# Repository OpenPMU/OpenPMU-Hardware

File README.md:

# OpenPMU Hardware
Reference materials for the OpenPMU V2 hardware for use by qualified professionals.

**Disclaimer:**  These files are **not** intended as a guide for how to build the hardware.  Such activities should only be conducted by suitably qualified professionals in a laboratory environment.

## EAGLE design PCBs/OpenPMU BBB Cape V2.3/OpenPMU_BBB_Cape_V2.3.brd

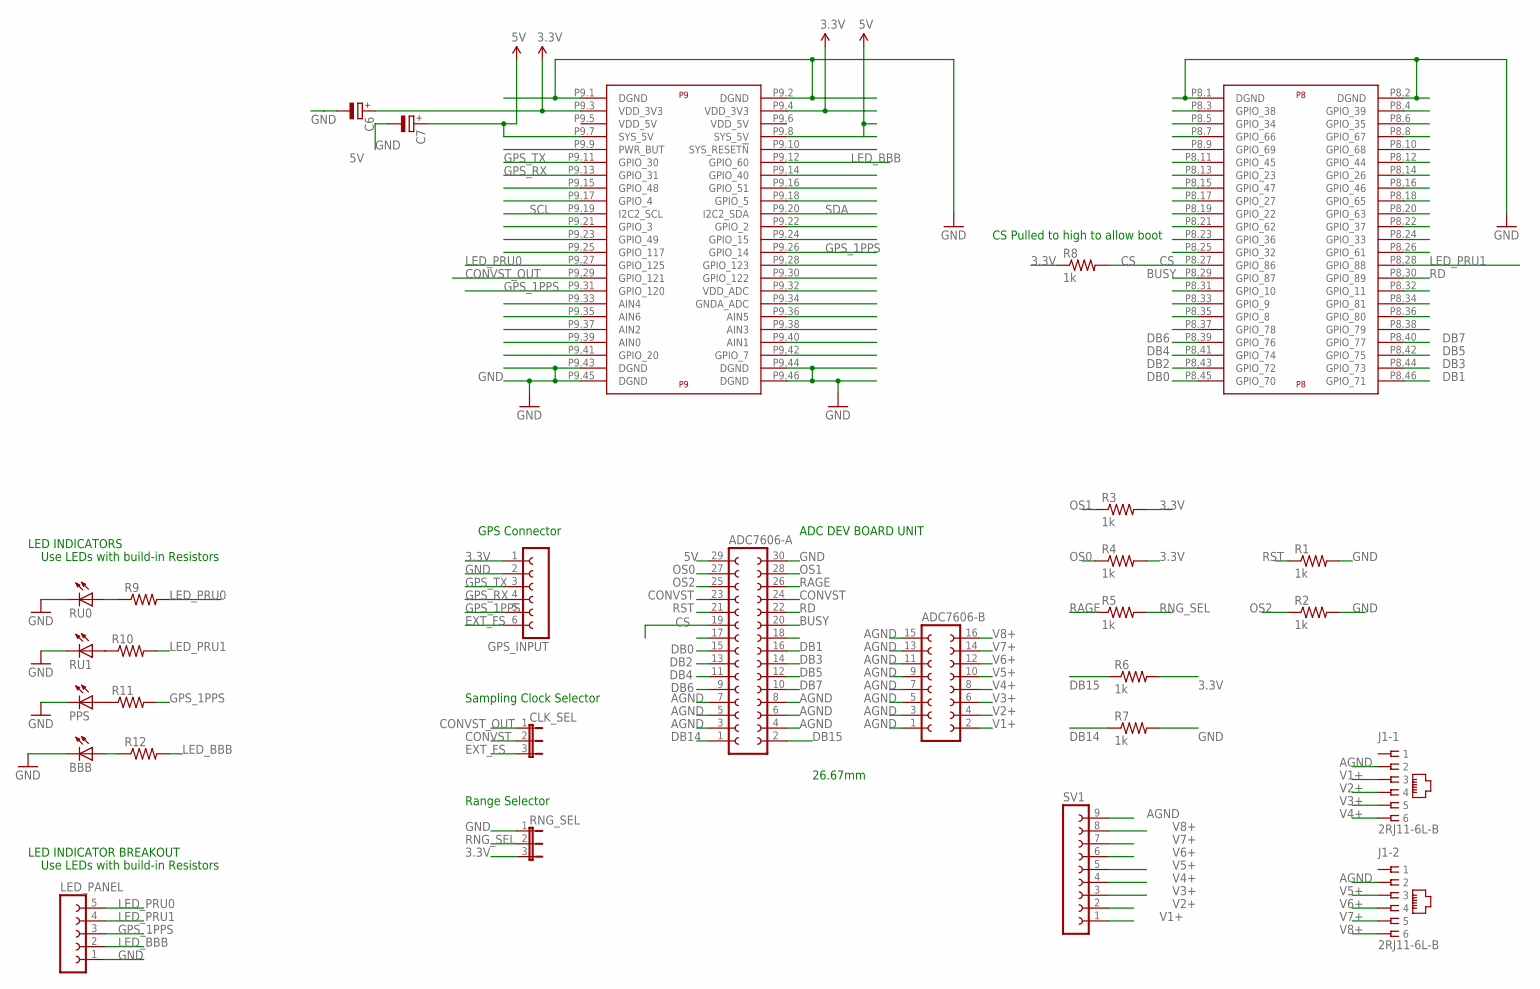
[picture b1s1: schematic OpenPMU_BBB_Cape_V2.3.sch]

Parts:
ADC7606-A: FE15-2
ADC7606-B: FE08-2
BBB: LEDCHIPLED_1206; CHIPLED_1206
C6, C7: CPOL-EUE1.8-4; E1,8-4
CLK_SEL: JP2E; JP2
GPS_INPUT: FE06-1; FE06
J1: 2RJ11-6L-B; 2RJ11
LED_PANEL: FE05-1
PPS: LEDCHIPLED_1206; CHIPLED_1206
R1, R2, R3, R4, R5, R6, R7, R8: 1k; 0204/7
R9, R10, R11, R12: R-US_M1206; M1206
RNG_SEL: JP2E; JP2
RU0, RU1: LEDCHIPLED_1206; CHIPLED_1206
SV1: FE09-1; FE09
U$1: BEAGLE_BONE_BLACK_CAPE

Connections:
3.3V: C6.+, GPS_INPUT.1, R3.2, R4.2, R6.2, R8.1, RNG_SEL.3, U$1.P9.3 (VDD_3V3), U$1.P9.4 (VDD_3V3)
5V: ADC7606-A.29, C7.+, U$1.P9.7 (SYS_5V), U$1.P9.8 (SYS_5V)
AGND: ADC7606-A.3, ADC7606-A.4, ADC7606-A.5, ADC7606-A.6, ADC7606-A.7, ADC7606-A.8, ADC7606-B.1, ADC7606-B.3, ADC7606-B.5, ADC7606-B.7, ADC7606-B.9, ADC7606-B.11, ADC7606-B.13, ADC7606-B.15, J1.1-2 (2), J1.2-2 (2), SV1.9
BUSY: ADC7606-A.20, U$1.P8.29 (GPIO_87)
CONVST: ADC7606-A.23, ADC7606-A.24, CLK_SEL.2
CONVST_OUT: CLK_SEL.1, U$1.P9.29 (GPIO_121)
CS: ADC7606-A.19, R8.2, U$1.P8.27 (GPIO_86)
DB0: ADC7606-A.15, U$1.P8.45 (GPIO_70)
DB1: ADC7606-A.16, U$1.P8.46 (GPIO_71)
DB2: ADC7606-A.13, U$1.P8.43 (GPIO_72)
DB3: ADC7606-A.14, U$1.P8.44 (GPIO_73)
DB4: ADC7606-A.11, U$1.P8.41 (GPIO_74)
DB5: ADC7606-A.12, U$1.P8.42 (GPIO_75)
DB6: ADC7606-A.9, U$1.P8.39 (GPIO_76)
DB7: ADC7606-A.10, U$1.P8.40 (GPIO_77)
DB14: ADC7606-A.1, R7.1
DB15: ADC7606-A.2, R6.1
EXT_FS: CLK_SEL.3, GPS_INPUT.6
FRST: ADC7606-A.18
GND: ADC7606-A.30, BBB.C, C6.-, C7.-, GPS_INPUT.2, LED_PANEL.1, PPS.C, R1.2, R2.2, R7.2, RNG_SEL.1, RU0.C, RU1.C, U$1.P8.1 (DGND), U$1.P8.2 (DGND), U$1.P9.1 (DGND), U$1.P9.2 (DGND), U$1.P9.43 (DGND), U$1.P9.44 (DGND), U$1.P9.45 (DGND), U$1.P9.46 (DGND)
GPS_1PPS: GPS_INPUT.5, LED_PANEL.3, R11.2, U$1.P9.26 (GPIO_14), U$1.P9.31 (GPIO_120)
GPS_RX: GPS_INPUT.4, U$1.P9.13 (GPIO_31)
GPS_TX: GPS_INPUT.3, U$1.P9.11 (GPIO_30)
LED_BBB: LED_PANEL.2, R12.2, U$1.P9.12 (GPIO_60)
LED_PRU0: LED_PANEL.5, R9.2, U$1.P9.27 (GPIO_125)
LED_PRU1: LED_PANEL.4, R10.2, U$1.P8.28 (GPIO_88)
unnamed: R9.1, RU0.A
unnamed: R10.1, RU1.A
unnamed: PPS.A, R11.1
unnamed: BBB.A, R12.1
OS0: ADC7606-A.27, R4.1
OS1: ADC7606-A.28, R3.1
OS2: ADC7606-A.25, R2.1
RAGE: ADC7606-A.26, R5.1
RD: ADC7606-A.22, U$1.P8.30 (GPIO_89)
RNG_SEL: R5.2, RNG_SEL.2
RST: ADC7606-A.21, R1.1
SCL: U$1.P9.19 (I2C2_SCL)
SDA: U$1.P9.20 (I2C2_SDA)
V1+: ADC7606-B.2, J1.1-3 (3), SV1.1
V2+: ADC7606-B.4, J1.1-4 (4), SV1.2
V3+: ADC7606-B.6, J1.1-5 (5), SV1.3
V4+: ADC7606-B.8, J1.1-6 (6), SV1.4
V5+: ADC7606-B.10, J1.2-3 (3), SV1.5
V6+: ADC7606-B.12, J1.2-4 (4), SV1.6
V7+: ADC7606-B.14, J1.2-5 (5), SV1.7
V8+: ADC7606-B.16, J1.2-6 (6), SV1.8
VI0: ADC7606-A.17

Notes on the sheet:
ADC DEV BOARD UNIT
GPS Connector
CS Pulled to high to allow boot
Sampling Clock Selector
LED INDICATORS
LED INDICATOR BREAKOUT
Use LEDs with build-in Resistors
26.67mm
Range Selector

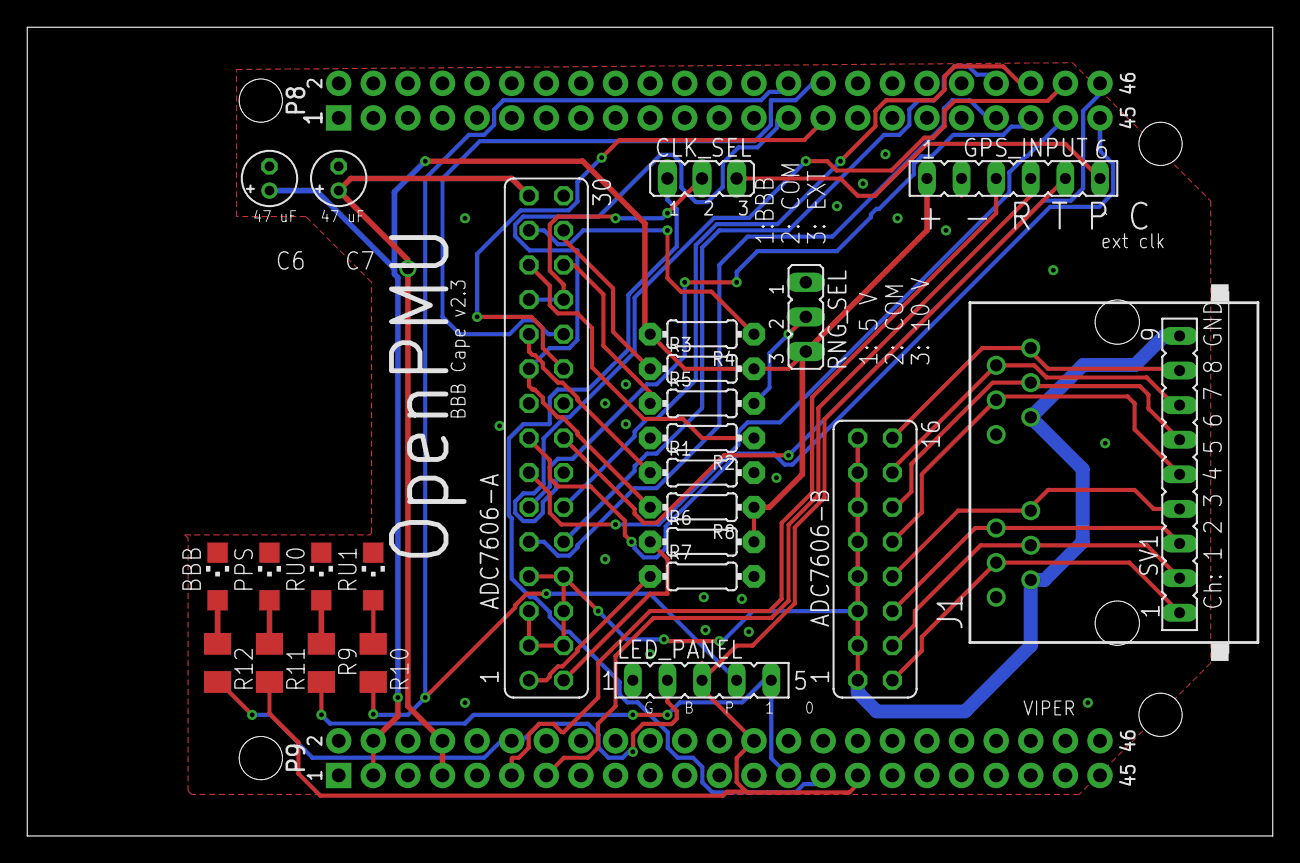
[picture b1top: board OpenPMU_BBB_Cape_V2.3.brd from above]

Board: 2 copper layers, 91.4 x 59.3 mm, 27 parts (0 on the bottom side), 44 nets.

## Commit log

2022-08-16 Rename Readme.MD to README.md

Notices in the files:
parts and their libraries:
SparkFun-Boards: Licensing: CC v3.0 Share-Alike You are welcome to use this library for commercial purposes.
